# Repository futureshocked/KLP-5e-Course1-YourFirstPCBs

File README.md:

# KLP 5e — Course 1: Your First PCBs — project files

Companion project files for *KiCad Like a Pro, 5th Edition*, Course 1 ("Your first
PCBs"). Each hands-on project is captured as a series of numbered stages, one per build
step in the course, so you can start from any point or check your own work against a
known-good result.

Clone this repository, or download the stage folder you need, open it in KiCad's project
manager, and carry on from there.

## About the course and the book series

To learn more about Course 1 and the *KiCad Like a Pro, 5th Edition* book series,
visit the [KLP 5e course page](https://techexplorations.com/kicad/course/).

## The sixteen-step card

The workflow from Module 2 on one printable page is in [`sixteen-steps/`](sixteen-steps/). Keep it open while you design your own board.

## Projects

| Folder | Project | Used in |
|---|---|---|
| [`klp5e-c1-blinky/`](klp5e-c1-blinky/) | The 555 LED blinker | Module 1 |
| [`klp5e-c1-a31-sourcing/`](klp5e-c1-a31-sourcing/) | Activity A3.1: source a part you have never used (task, record sheet, worked solution) | Module 3 |
| [`klp5e-c1-m4-breadboard-psu/`](klp5e-c1-m4-breadboard-psu/) | The breadboard power supply, from schematic to the files for the manufacturer | Modules 4 and 6 |
| [`klp5e-c1-m5-solar-psu/`](klp5e-c1-m5-solar-psu/) | The tiny solar power supply | Module 5 |

See each project's own README for what each stage contains.

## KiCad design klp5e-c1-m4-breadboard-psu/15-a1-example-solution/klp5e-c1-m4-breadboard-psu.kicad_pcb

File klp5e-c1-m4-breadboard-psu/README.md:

# klp5e-c1-m4-breadboard-psu stages

One folder per step of the breadboard power supply, used by Course 1 Modules 4 and 6 and
Activity A4.1. Each stage is the project as it stood at the end of a lecture and the start of the
next one. Open the `.kicad_pro` file inside a stage folder in KiCad.

The project starts from the end of Module 3, so the first stage is `03`. J1 is the USB-C
connector you sourced in Module 3; its symbol and footprint live in each stage's `Libraries/`
folder. The footprint library is `Libraries/Footprints.pretty`: a footprint library is a folder
whose name ends in `.pretty`. The Module 3 and 4 videos show the folder under its old name,
`Footprints`. KiCad loads it either way, and the library's nickname is `Footprints` in both, so
nothing else changes.

| Stage | State |
|---|---|
| `03-project-ready` | New project with Module 3's libraries copied in and registered |
| `04-symbols-placed` | Every symbol placed and annotated, no wires |
| `05-wired` | Schematic wired, including the no-connect flag on SW1 and the shield to ground |
| `06-values-set` | Resistor and capacitor values set (F1 keeps `Polyfuse` until Module 6) |
| `07-footprints-assigned` | Every symbol has a footprint |
| `08-erc-clean` | Power flags added; the electrical rules check reports 0 errors |
| `09-outline-drawn` | Footprints imported into the board and the outline drawn |
| `10-parts-placed` | Connectors on the edges, the rest placed, outline trimmed and its corners rounded |
| `11-routed` | Power and signal tracks routed at 0.8 mm and 0.4 mm, ground left for the pour |
| `12-ground-poured` | Ground plane poured on the bottom layer |
| `13-drc-clean` | The four shield tracks added; DRC reports 0 errors and 0 unconnected items |
| `14-silkscreen-done` | Designators resized and labels added on the silkscreen; the finished Module 4 board and the start of A4.1 |
| `15-a1-example-solution` | A4.1's worked solution: J3 added to feed the far rail of the breadboard |
| `16-ready-to-order` | The Module 6 result: F1 set to `500mA`, the bill of materials (`klp5e-c1-m4-breadboard-psu.csv`), and in `c1-m4-breadboard-psu/` the seven Gerber layers, the job file, one drill file and the zip you upload to the manufacturer |

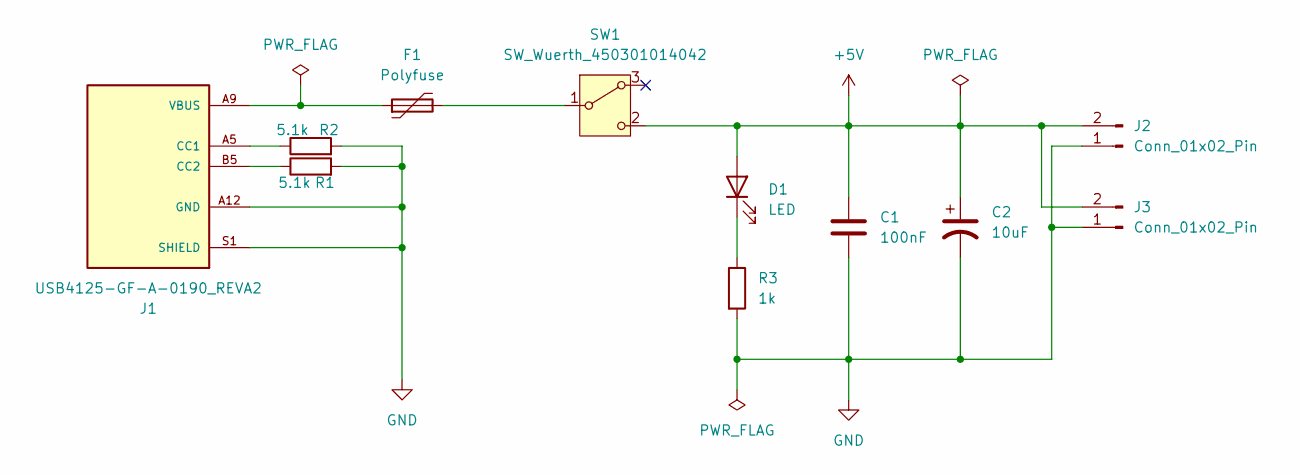
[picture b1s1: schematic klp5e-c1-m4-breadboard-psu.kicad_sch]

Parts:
C1: 100nF; C_Disc_D3.0mm_W1.6mm_P2.50mm
C2: 10uF; CP_Radial_D4.0mm_P1.50mm
D1: LED; LED_D5.0mm
F1: Polyfuse; Fuse_Bourns_MF-RHT050
J1: USB4125-GF-A-0190_REVA2; GCT_USB4125-GF-A-0190_REVA2; PARTREV Rev A2
J2, J3: Conn_01x02_Pin; PinHeader_1x02_P2.54mm_Vertical
R1, R2: 5.1k; R_Axial_DIN0204_L3.6mm_D1.6mm_P5.08mm_Horizontal
R3: 1k; R_Axial_DIN0204_L3.6mm_D1.6mm_P5.08mm_Horizontal
SW1: SW_Wuerth_450301014042; SW_Slide-03_Wuerth-WS-SLTV_10x2.5x6.4_P2.54mm

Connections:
+5V: C1.1, C2.1, D1.2 (A), J2.2, J3.2, SW1.2 (C)
GND: C1.2, C2.2, J1.A12 (GND), J1.B12 (GND), J1.S1 (SHIELD), J1.S2 (SHIELD), J1.S3 (SHIELD), J1.S4 (SHIELD), J2.1, J3.1, R1.2, R2.2, R3.2
unnamed: D1.1 (K), R3.1
unnamed: J1.A5 (CC1), R2.1
unnamed: J1.B5 (CC2), R1.1
unnamed: F1.2, SW1.1 (B)
VBUS: F1.1, J1.A9 (VBUS), J1.B9 (VBUS)

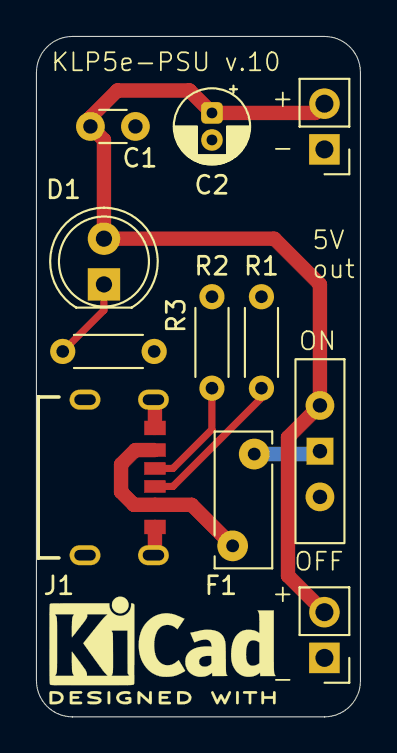
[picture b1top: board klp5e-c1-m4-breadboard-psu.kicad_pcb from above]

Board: 2 copper layers, 18.0 x 37.8 mm, 11 parts (0 on the bottom side), 7 nets.

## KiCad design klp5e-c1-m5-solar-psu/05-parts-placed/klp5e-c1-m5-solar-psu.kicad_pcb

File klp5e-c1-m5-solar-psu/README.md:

# klp5e-c1-m5-solar-psu stages

One folder per step of the tiny solar power supply, used by Course 1 Module 5 and Activities
A5.1 and A5.2. Each stage is the project as it stood at the end of a lecture and the start of the
next one. Open the `.kicad_pro` file inside a stage folder in KiCad.

The three imported footprints live in `Libraries/footprints.pretty`, one footprint library for
the whole project. A footprint library is a folder whose name ends in `.pretty`; Chapter 6 of
the book explains why. In the lecture 5.2 video the folder is still called `footprints`, its old
name. KiCad loads it either way, and the library's nickname is `footprints` in both, so nothing
else changes.

| Stage | State |
|---|---|
| `00-libraries-waiting` | New project, the three part libraries not yet registered |
| `01-libraries-registered` | Symbol and footprint libraries registered |
| `02-annotated` | Symbols placed and annotated |
| `03-values-set` | Sixteen parts named and valued, no wires (the start of A5.1) |
| `04-schematic-complete` | Schematic fully wired |
| `04b-erc-clean` | Schematic wired and the electrical rules check clean |
| `05-parts-placed` | Footprints imported and placed on the board, no outline tightened yet |
| `06-outline-tightened` | Board outline shrunk to fit and its corners rounded |
| `07-routed` | Every connection except ground routed on the top layer |
| `08-drc-clean` | Ground pour and stitching via added; DRC reports 0 errors and 0 unconnected items |
| `09-silkscreen-done` | Reference designators resized and moved, text added on the silkscreen |
| `10-3d-models` | 3D models attached; the finished board (the worked solution for A5.2) |

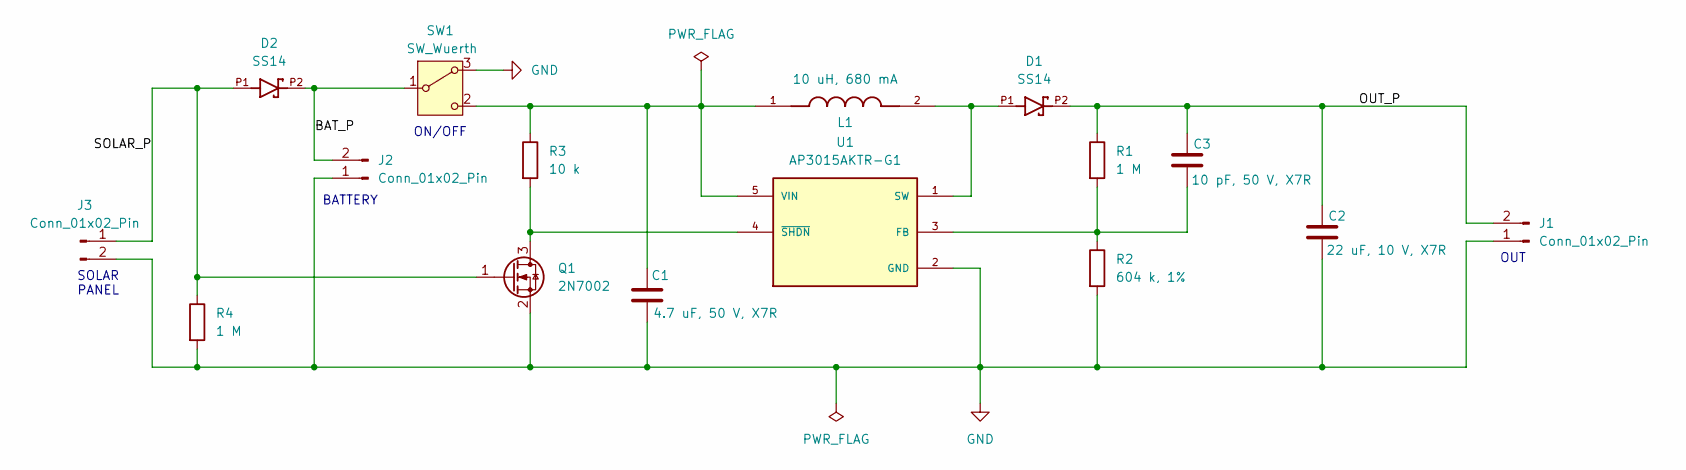
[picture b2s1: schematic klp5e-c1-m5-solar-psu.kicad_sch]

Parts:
C1: 4.7 uF, 50 V, X7R; C_Disc_D5.0mm_W2.5mm_P2.50mm
C2: 22 uF, 10 V, X7R; C_Radial_D5.0mm_H11.0mm_P2.00mm
C3: 10 pF, 50 V, X7R; C_Disc_D5.0mm_W2.5mm_P2.50mm
D1, D2: SS14; SMA
J1, J2, J3: Conn_01x02_Pin; PinHeader_1x02_P2.54mm_Vertical
L1: 10 uH, 680 mA; IND_ASPI-0630LR-100M-T15; PARTREV B
Q1: 2N7002; SOT-23
R1, R4: 1 M; R_Axial_DIN0204_L3.6mm_D1.6mm_P5.08mm_Horizontal
R2: 604 k, 1%; R_Axial_DIN0204_L3.6mm_D1.6mm_P5.08mm_Horizontal
R3: 10 k; R_Axial_DIN0204_L3.6mm_D1.6mm_P5.08mm_Horizontal
SW1: SW_Wuerth; SW_Slide-03_Wuerth-WS-SLTV_10x2.5x6.4_P2.54mm
U1: AP3015AKTR-G1; SOT95P280X145-5N; PARTREV 1.4

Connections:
/BAT_P: D2.P2, J2.2, SW1.1 (B)
/OUT_P: C2.1, C3.1, D1.P2, J1.2, R1.1
/SOLAR_P: D2.P1, J3.1, Q1.1 (G), R4.1
GND: C1.2, C2.2, J1.1, J2.1, J3.2, Q1.2 (S), R2.2, R4.2, SW1.3 (A), U1.2 (GND)
unnamed: Q1.3 (D), R3.2, U1.4 (~SHDN)
unnamed: C1.1, L1.1, R3.1, SW1.2 (C), U1.5 (VIN)
unnamed: C3.2, R1.2, R2.1, U1.3 (FB)
unnamed: D1.P1, L1.2, U1.1 (SW)

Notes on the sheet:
SOLAR PANEL
BATTERY
ON/OFF
OUT

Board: 2 copper layers, 16 parts (0 on the bottom side), 8 nets, no tracks yet.

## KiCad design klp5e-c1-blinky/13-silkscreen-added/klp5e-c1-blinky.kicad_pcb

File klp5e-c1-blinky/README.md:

# klp5e-c1-blinky — the blinker, staged

The blinker board from Course 1, Module 1, captured as one folder per build step. Stage N
is the project exactly as it stood at the end of the lecture that produced it, and the
start of the next one.

Open a stage in KiCad's project manager and carry on from the next lecture, or use one as
a restart point if a step went wrong.

| Stage | State | Lecture |
|---|---|---|
| `00-project-created` | Project created, sheet blank | L1.1 |
| `01-symbols-placed` | Symbols placed, unannotated, nothing wired | L1.2 |
| `02-annotated` | Every designator assigned | L1.3 |
| `03-values-set` | All values set | L1.4 |
| `04-wired` | Fully wired | L1.5 |
| `05-footprints-assigned` | Every symbol footprinted | L1.6 |
| `06-erc-clean` | ERC clean, schematic complete | L1.7 |
| `07-parts-imported` | Parts imported to the board | L1.8 |
| `08-bearings` | Board editor set up | L1.9 |
| `09-outline-drawn` | Board outline drawn | L1.10 |
| `10-parts-placed` | Components placed | L1.11 |
| `11-routed` | Tracks routed | L1.12 |
| `12-ground-poured` | Ground pour added | L1.13 |
| `13-silkscreen-added` | Silkscreen text added | L1.15 |
| `14-plotted` | Finished board, plotted to `Gerbers-blinky/` | L1.16 |

`14-plotted` is the finished board. If you build the blinker yourself in activity A1.1,
compare your result against this stage, not against the exact steps that got you there.

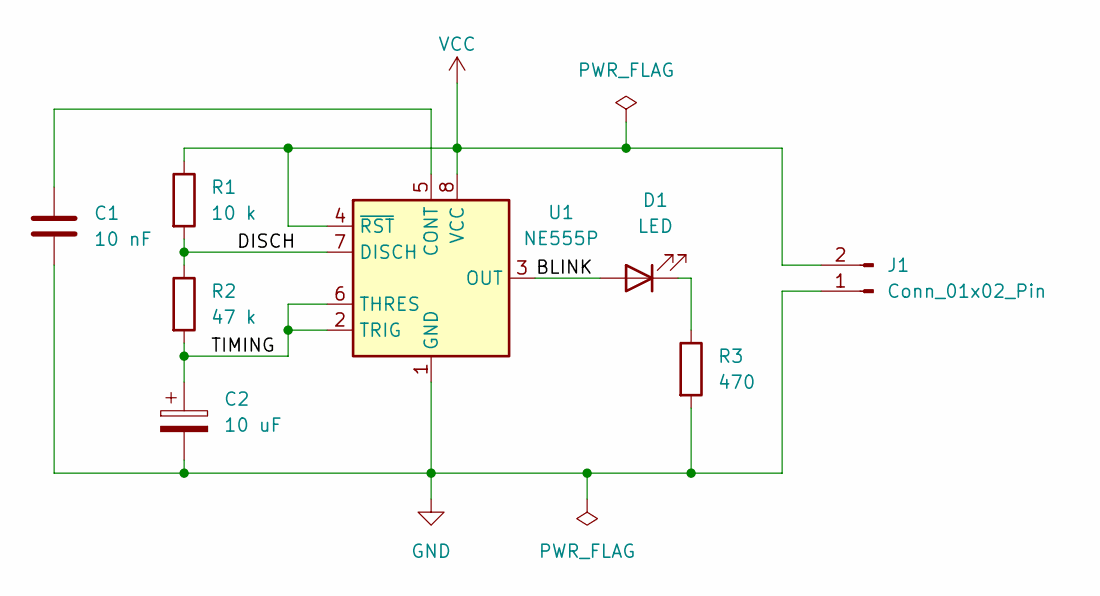
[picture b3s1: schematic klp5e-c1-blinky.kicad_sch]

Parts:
C1: 10 nF; C_Disc_D3.0mm_W2.0mm_P2.50mm
C2: 10 uF; C_Radial_D4.0mm_H5.0mm_P1.50mm
D1: LED; LED_D5.0mm
J1: Conn_01x02_Pin; PinHeader_1x02_P2.54mm_Vertical
R1: 10 k; R_Axial_DIN0204_L3.6mm_D1.6mm_P5.08mm_Horizontal
R2: 47 k; R_Axial_DIN0204_L3.6mm_D1.6mm_P5.08mm_Horizontal
R3: 470; R_Axial_DIN0204_L3.6mm_D1.6mm_P5.08mm_Horizontal
U1: NE555P; DIP-8_W7.62mm

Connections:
/BLINK: D1.2 (A), U1.3 (OUT)
/DISCH: R1.2, R2.1, U1.7 (DISCH)
/TIMING: C2.1, R2.2, U1.2 (TRIG), U1.6 (THRES)
GND: C1.2, C2.2, J1.1, R3.2, U1.1 (GND)
unnamed: D1.1 (K), R3.1
unnamed: C1.1, U1.5 (CONT)
VCC: J1.2, R1.1, U1.4 (~RST), U1.8 (VCC)

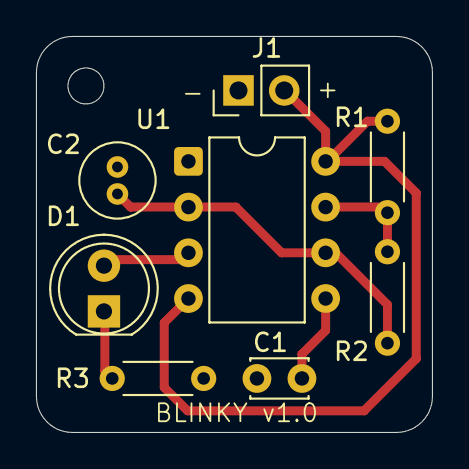
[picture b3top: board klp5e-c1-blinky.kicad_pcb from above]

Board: 2 copper layers, 22.0 x 22.0 mm, 8 parts (0 on the bottom side), 7 nets.
